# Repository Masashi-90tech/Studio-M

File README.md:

# Studio M

> DIYのための、設計・解析・製作がつながる工房

「このブラケットは5kgに耐える？」「このケースは何℃になる？」。
DIY で何かを作るとき、知りたいのはたいていこうした問いです。Studio M は、その問いから完成した部品までを一本の流れで案内するツールです。

FreeCAD は何でもできる道具箱です。Studio M は道具箱を渡す代わりに、**目的から入る体験**を用意します。

## 設計思想

**エンジンは借りる、体験は自作。**

流体・熱・強度の計算には、実績のあるオープンソースのソルバーを使います。その上の「問いを立てる」「条件を置く」「結果を読む」部分は Studio M が自前で作り、分かりやすい日本語の体験にします。

## 現在の機能（Studio M Lite / 段階0）

ブラウザで動く解析環境です。2D の断面で解くのが基本で、3D モデルの熱と流れは 3D のままでも解けます（[docs/3D.md](docs/3D.md)）。

- **形状描画**: 矩形・円・多角形・フリーハンドで断面を描く
- **役割の割り当て**: 物体、発熱体、穴、温度固定、支持、荷重
- **材料**: PLA, PETG, ABS, A6061, A5052, SS400, SUS304, C1100, FR-4, 空気, 水
- **解析**
  - 流れ: 格子ボルツマン法（D2Q9 + Smagorinsky）。カルマン渦列、抗力・揚力を確認。「温度も計算する（風で冷やす）」をオンにすると、同じ格子で温度の移流拡散も解き（共役伝熱）、ファンの風でヒートシンクや部品が何℃になるかを調べられる（PC の本計算 OpenFOAM は流れだけ）
  - 熱: 定常熱伝導（有限体積法）。周囲への対流を含む
  - 強度: 2D 平面応力の有限要素法（Q4 要素）。von Mises 応力と安全率
  - 対流拡散: 「@CFDbyHand」の Excel 例「一様流中の四角柱まわり」を再現
- **KiCad 基板の熱**: 「ファイル」→「KiCad基板を開く」（または作図エリアへ .kicad_pcb をドロップ）で、基板の形・銅箔・部品の位置を取り込み、部品ごとの発熱（ライブラリの目安値を書き換え可）から基板の温度を解く。手元に基板がなければ「サンプル基板で試す」。ファイルはブラウザの中だけで処理し、通信しない
- **3D モデルの断面**: 「ファイル」→「3Dモデルを開く（STL・OBJ）」（または作図エリアへ .stl / .obj をドロップ）で、Blender や CAD のモデルを 3D で見ながら切る面（X / Y / Z と位置）を選び、その断面を外形と穴の 2D の形にして、流れ・熱・強度・電磁波の解析にかける。穴のあるモデル（水密でない）は注意を出し、重なった頂点などは自動で直す。手元にモデルがなければ「サンプル（穴のあいた板）で試す」。ファイルはブラウザの中だけで処理し、通信しない
- **3D のまま解く（熱・流れ）**: 取り込みダイアログの「3D のまま解析する」で 3D 解析の画面を開く。**熱**は、面をクリックして発熱・温度固定・ファン・断熱を置き、部品の中の温度を表面の色と断面で見る。**流れ**は、部品を風洞に置いて風の向きと速さを選び、表面の圧力・断面の流速・3D の流線と、抗力・抗力係数を見る（止めるまで進む計算。一時停止・再開あり）。どちらも形を小さな立方体（ボクセル）に分けてブラウザで解く。使い方・精度・限界は [docs/3D.md](docs/3D.md)
- **部品ごとの温度**: 熱の結果の下に、部品ごとの最高温度・上限温度との差を表で出す。判定カードは一番熱い部品を名指しし、冷却（自然放置・ファン）を切り替えて温度の下がり方を比べられる
- **数学の窓**（学習機能をオンにすると出ます）: 判定カードの下に「この答えの式」を出し、今の数値を代入して見せる。スライダーで変数を動かすと結果と一言（例: 長さ 2 倍 → たわみ 8 倍）が変わる
- **学習機能の切り替え**: 数学の窓と学ぶモードは、ヘッダーの設定（⚙）の「学習機能を表示する」で出し入れする。既定はオフ（画面がすっきり）で、オフのあいだは学習用の部品を読み込まない。設定はブラウザごとに保存
- **学ぶモード**（学習機能をオンにすると出ます）: ヘッダーの「学ぶ」から、理論 → やってみる → 確認問題 → 実践の 11 レッスン（中学・高校・大学の順）。プリセットを開いて、操作しながら進められる。進み具合はブラウザに保存
- **Excel 出力**
  - 結果ブック: 条件・形状・材料、温度や応力のヒートマップ（条件付き書式）、履歴
  - 数式ブック: Excel 自身が反復計算で対流拡散を解く（動画と同じ考え方）

## Studio M Engine（PC で本計算）

Lite はブラウザの中の簡易な計算です。もっと確かな答えが欲しいときは、この PC の上で **Studio M Engine** を動かし、
**CalculiX**（強度）や **OpenFOAM**（流れ）で「本計算」できます。結果は Lite の結果と切り替えたり、代表値を並べて比べたりできます。

```bash
npm run engine     # エンジンを起動（Node.js 22 以上）。画面に URL と合言葉が出る
```

1. ダウンロードした HTML（または `npm run dev` の開発版）で Studio M を開く
2. ⚙ 設定 →「PCのエンジン」に URL と合言葉を貼り付けて「接続を確認」
3. 強度・流れのタブで「本計算で解く」→ 進み具合 → 完了後に「Lite ⇄ 本計算」と比較表

- 解析ソフトは別プロセスとして呼ぶだけで、Studio M には同梱しません（GPL）。入れ方（Ubuntu / Docker / Windows の WSL / macOS）は [docs/ENGINE.md](docs/ENGINE.md)
- **安全**: エンジンは `127.0.0.1` だけで待ち受け、起動のたびに作る合言葉がないと答えません。画面から受け取るのは形と条件の JSON だけで、ファイルのパスや命令は受け取りません
- claude.ai に公開したページ（Artifact）からは PC のエンジンに届きません。ダウンロードした HTML か開発版で使ってください

## 精度についての注意

- 結果は**傾向と比較**のためのものです。絶対値として設計判断に使わないでください。
- 2D の近似です。奥行き方向には一定の厚さの板として扱います。
- 3D プリントの部品は Z 方向（積層方向）の強度が弱くなります。
- 安全に関わる用途では、必ず専門のツールで検証してください。

## はじめかた

Node.js と npm が必要です。

```bash
npm install       # 依存関係をインストール
npm run dev       # 開発サーバーを起動
npm test          # テストを実行（vitest）
npm run build     # 型チェックのあと、dist/ に単一の HTML ファイルを出力
npm run engine    # PC のエンジン（Studio M Engine）を起動。本計算に使う
npm run check     # 型チェック + テスト + ライセンス確認
```

`npm run build` の結果は、外部ファイルなしで単体で動く HTML です。

## 仕組み（要点）

- **座標と格子**: 単位はメートル。原点は解析領域の左下。セルは正方形で、格子の幅は `domain.width / nx` で決まります。
- **共通データモデル**: 描画・ソルバー・Excel 出力は、すべて `src/core/types.ts` の型だけを介してやり取りします。
- **少しずつ計算する**: ソルバーは `step(budgetMs)` で時間を区切って計算を進めます。画面は計算の合間に結果を描くため、固まらずに進み具合を見られます。
- **形状の重ね順**: 形状は配列の順に適用され、後のものが前のものを上書きします。穴あけは、それより前に置かれた物体を削ります。

## ディレクトリ構成

```
src/
├── core/      共通データモデル（types.ts）、材料（materials.ts）、格子化（raster.ts）、初期値（project.ts）
├── solvers/   流れ・熱・強度・対流拡散・電磁波のソルバー（2D）と、3D の熱（heat3d）・流れ（flow3d）
├── export/    Excel 出力
engine/        Studio M Engine（PC 上の Node.js サーバー）: server/（HTTP・ジョブ・実行）、adapters/（CalculiX・OpenFOAM の変換役）
├── workbench/ 解析 1 つ分のまとめ（ソルバー・パネル・判定・プリセット・数学の窓）と登録表
├── pcb/       KiCad 基板の取り込み（読み取り・部品ライブラリ・熱プロジェクトの組み立て・ダイアログ）
├── mesh3d/    3D モデル（STL・OBJ）の取り込み（読み取り・メッシュの整理・断面・3D ビューア・ダイアログ）
├── sim3d/     3D 解析の画面（熱・流れ。面の条件・結果の色・断面・流線）
├── learn/     数学の窓（式の提供者・部品）、レッスン、進み具合
├── ui/        エディタ、パネル、描画、プリセット、数学の窓のカード、「学ぶ」ドロワー
└── main.ts    エントリーポイント
```

## ロードマップ

段階ごとの計画と、使う予定のオープンソースは [docs/ROADMAP.md](docs/ROADMAP.md) にまとめています。

## ライセンス

- Studio M 自身のコード: MIT License
- OpenFOAM・CalculiX など GPL のツールは、Studio M Engine から**別プロセスとして呼び出す**だけで、Studio M のコードにはリンクも同梱もしません。

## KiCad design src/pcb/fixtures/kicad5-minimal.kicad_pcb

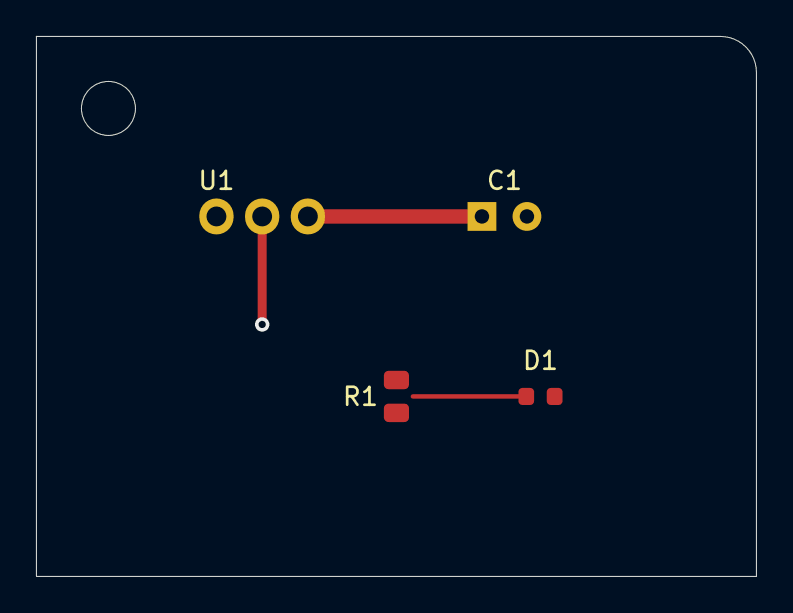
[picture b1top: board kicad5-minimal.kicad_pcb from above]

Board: 2 copper layers, 40.0 x 30.0 mm, 4 parts (0 on the bottom side), 2 nets.

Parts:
C1: 220uF; CP_Radial_D6.3mm_P2.50mm
D1: RED; LED_0603_1608Metric
R1: 10k; R_0805_2012Metric
U1: L7805; TO-220-3_Vertical

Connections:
+5V: C1.1, D1.2, R1.2, U1.3
GND: C1.2, D1.1, R1.1, U1.2

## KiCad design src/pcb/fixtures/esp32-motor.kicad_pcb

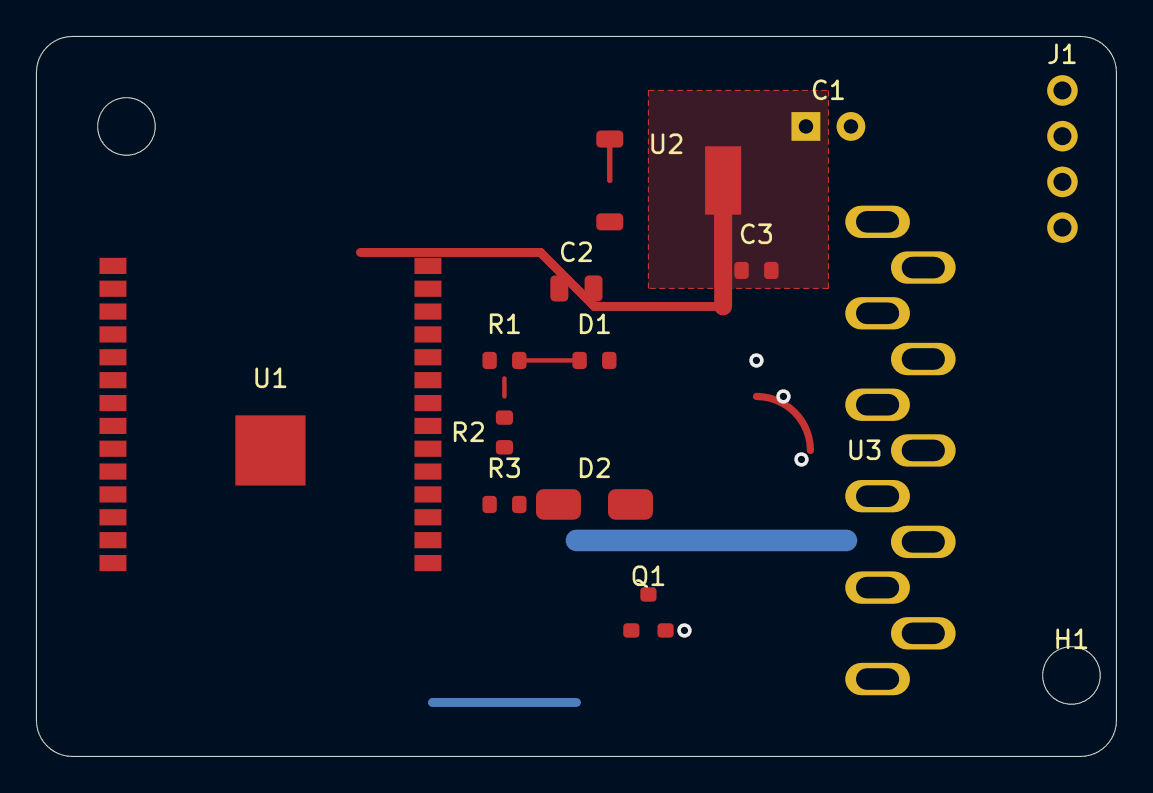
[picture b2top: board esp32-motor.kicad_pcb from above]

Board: 2 copper layers, 60.0 x 40.0 mm, 15 parts (1 on the bottom side), 3 nets.

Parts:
C1: 100uF; CP_Radial_D6.3mm_P2.50mm
C2: 10uF; C_0805_2012Metric
C3, C4: 100nF; C_0603_1608Metric
D1: GREEN; LED_0603_1608Metric
D2: SS34; D_SMA
H1: MountingHole; MountingHole_3.2mm_M3
J1: Conn_01x04; PinHeader_1x04_P2.54mm_Vertical
Q1: AO3400A; SOT-23
R1, R3: 10k; R_0603_1608Metric
R2: 330; R_0603_1608Metric
U1: ESP32-S3-WROOM-1-N8; ESP32-S3-WROOM-1
U2: AMS1117-3.3; SOT-223-3_TabPin2
U3: L298N; Multiwatt-11_Simplified

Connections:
+3V3: C1.1, C2.2, C3.2, C4.2, D1.2, D2.2, R1.2, R2.2, R3.2, U1.15, U2.2
+5V: U2.3, U3.4
GND: C1.2, C2.1, C3.1, C4.1, D1.1, D2.1, R1.1, R2.1, R3.1, U1.1, U1.14, U1.41, U2.1
